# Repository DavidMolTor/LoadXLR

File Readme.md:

# XLR Resistive Load

A load module for audio applications with balanced connections.

## Introduction

This module is designed to be used together with the Cosmos ADC from E1DA. It contains a set of 1-2W resistor for loading audio devices while performing performance measurements.

It contains left and right audio input and outputs via XLR connectors. Measuring probes can be connected using the PCB test points. The load value can be selected using the DIP switches.

## Features

 - Wide audio traces for minimal resistance.

 - Impedance matched traces around 100Ω.

 - Up to 32 load values via DIP switches.

 - Probe test points for measuring.

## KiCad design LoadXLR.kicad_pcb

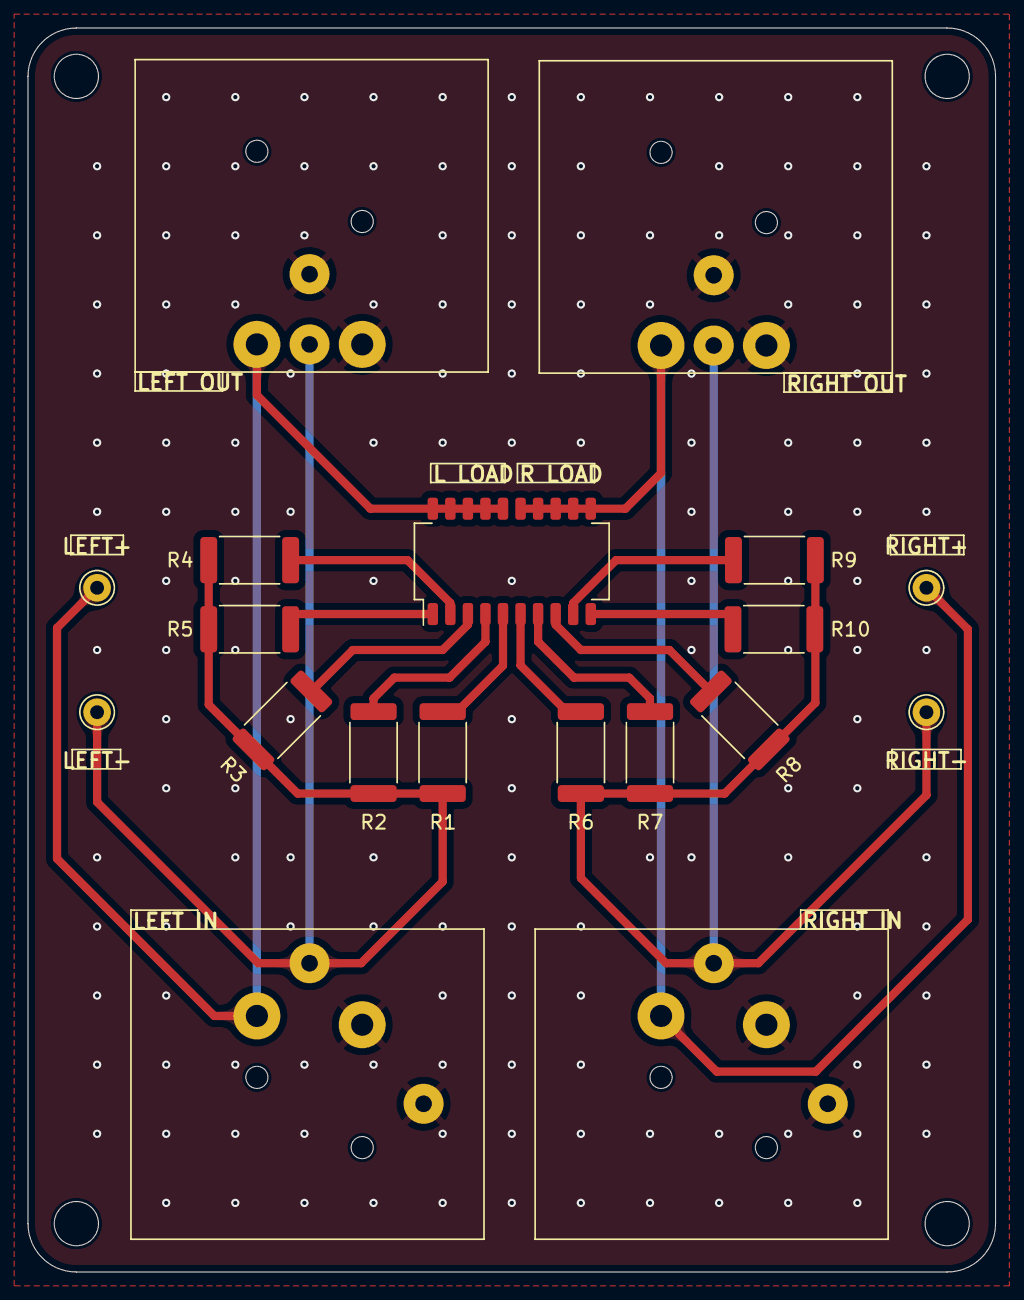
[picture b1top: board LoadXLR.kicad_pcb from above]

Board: 2 copper layers, 70.0 x 90.0 mm, 23 parts (0 on the bottom side), 15 nets.

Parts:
H1, H2, H3, H4: MountingHole; MountingHole_3.2mm_M3
J1, J3: NC3MAH; XLR_NEUTRIK_NC3MAH_HOR
J2, J4: NC3FAH2; XLR_NEUTRIK_NC3FAH2_HOR
R1, R6: 20; R_2512_6332Metric
R2, R7: 40; R_2512_6332Metric
R3, R8: 80; R_2512_6332Metric
R4, R9: 160; R_2512_6332Metric
R5, R10: 320; R_2512_6332Metric
SW1: SW_DIP_x10; SW_DIP_SPSTx10_Slide_Copal_CHS-10B_W7.62mm_P1.27mm
TP1: LEFT+; Pin_D1.0mm_L10.0mm
TP2: LEFT-; Pin_D1.0mm_L10.0mm
TP3: RIGHT+; Pin_D1.0mm_L10.0mm
TP4: RIGHT-; Pin_D1.0mm_L10.0mm

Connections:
/L+: J1.2, J2.2, SW1.16, SW1.17, SW1.18, SW1.19, SW1.20, TP1.1
/L-: J1.3, J2.3, R1.1, R2.1, R3.1, R4.2, R5.2, TP2.1
/R+: J3.2, J4.2, SW1.11, SW1.12, SW1.13, SW1.14, SW1.15, TP3.1
/R-: J3.3, J4.3, R6.1, R7.1, R8.1, R9.2, R10.2, TP4.1
GND: J1.1, J1.G, J2.1, J2.G, J3.1, J3.G, J4.1, J4.G
unnamed: R1.2, SW1.5
unnamed: R2.2, SW1.4
unnamed: R3.2, SW1.3
unnamed: R4.1, SW1.2
unnamed: R5.1, SW1.1
unnamed: R6.2, SW1.6
unnamed: R7.2, SW1.7
unnamed: R8.2, SW1.8
unnamed: R9.1, SW1.9
unnamed: R10.1, SW1.10

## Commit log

2025-06-28 Initial commit
    Added main project files.
2025-07-06 Board layout
    Updated the board layout.
    Added a picture of the board render.
2025-07-06 Readme
    Added a readme file for the project.
